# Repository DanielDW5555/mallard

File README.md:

# mallard
Ecological monitoring capstone for ECE 7000. The design will be a continuous redox measurement tool for peatlands.

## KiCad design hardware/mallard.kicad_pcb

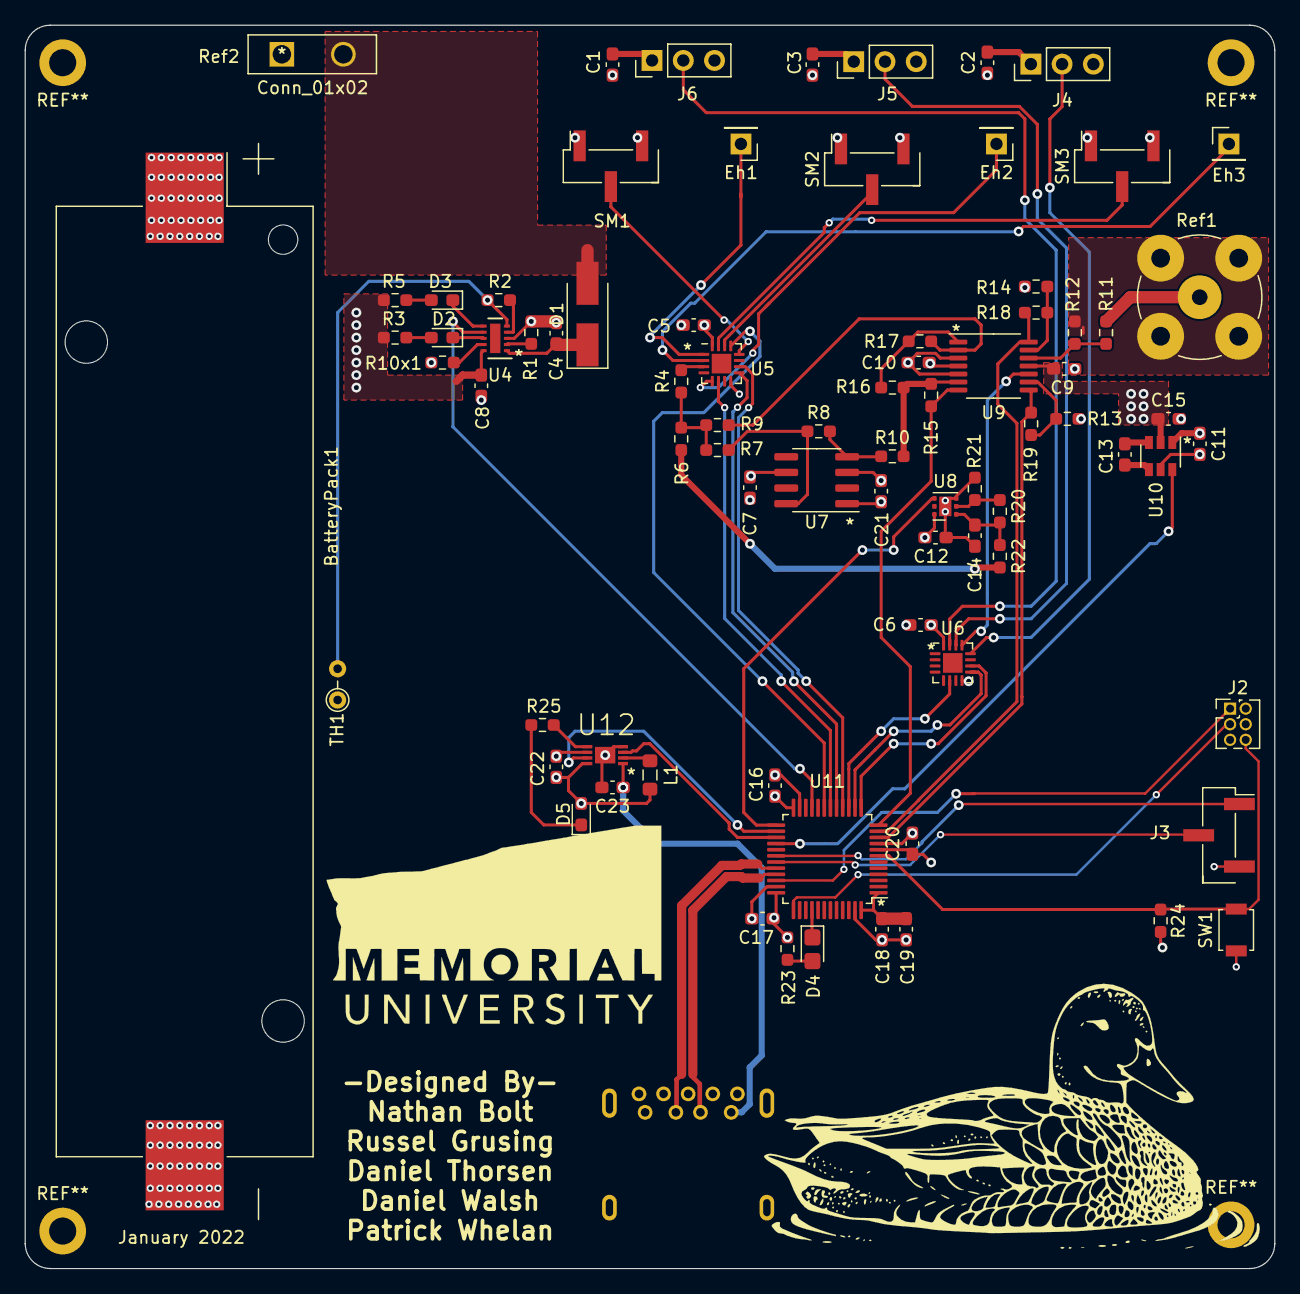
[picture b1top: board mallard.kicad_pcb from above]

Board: 4 copper layers, 101.6 x 101.1 mm, 81 parts (1 on the bottom side), 68 nets.

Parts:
BatteryPack1: 3.7V; BatteryHolder_Keystone_1042_1x18650
C1, C2, C3, C4, C5, C6, C7, C8, C9, C10, C12, C13, C14, C21: 1uF; C_0603_1608Metric_Pad1.08x0.95mm_HandSolder
C11, C15, C23: 10uF; C_0603_1608Metric_Pad1.08x0.95mm_HandSolder
C16, C17, C18, C19, C20: 0.1uF; C_0603_1608Metric_Pad1.08x0.95mm_HandSolder
C22: 3.3uF; C_0603_1608Metric_Pad1.08x0.95mm_HandSolder
D1: D; D_SMA_Handsoldering
D2, D3: LED; LED_0603_1608Metric_Pad1.05x0.95mm_HandSolder
D4: Orange; D_0805_2012Metric_Castellated
D5: RED; LED_0603_1608Metric_Pad1.05x0.95mm_HandSolder
Eh1, Eh2, Eh3: Eh Electrode; PinHeader_1x01_P2.54mm_Vertical
J1: USB_A; USB3_A_Molex_48393-001
J2: Conn_02x03_Odd_Even; PinHeader_2x03_P1.27mm_Vertical
J3: Conn_01x03; PinHeader_1x03_P2.54mm_Vertical_SMD_Pin1Right
J4, J5, J6: Conn_01x03; PinHeader_1x03_P2.54mm_Vertical
L1: 4.7uH; L_0805_2012Metric_Pad1.05x1.20mm_HandSolder
R1, R10x1: 5.1k; R_0603_1608Metric_Pad0.98x0.95mm_HandSolder
R2: 21.5k; R_0603_1608Metric_Pad0.98x0.95mm_HandSolder
R3, R5: 3.6k; R_0603_1608Metric_Pad0.98x0.95mm_HandSolder
R4, R6, R8, R13, R17, R24: 10k; R_0603_1608Metric_Pad0.98x0.95mm_HandSolder
R7, R11, R12, R22: Jumper; R_0603_1608Metric_Pad0.98x0.95mm_HandSolder
R9: Jumper DNI; R_0603_1608Metric_Pad0.98x0.95mm_HandSolder
R10, R19: 20k; R_0603_1608Metric_Pad0.98x0.95mm_HandSolder
R14: 1k; R_0603_1608Metric_Pad0.98x0.95mm_HandSolder
R15: 30k; R_0603_1608Metric_Pad0.98x0.95mm_HandSolder
R16: 20k DNI; R_0603_1608Metric_Pad0.98x0.95mm_HandSolder
R18: 9.1k; R_0603_1608Metric_Pad0.98x0.95mm_HandSolder
R20: 80.6k; R_0603_1608Metric_Pad0.98x0.95mm_HandSolder
R21: 324k; R_0603_1608Metric_Pad0.98x0.95mm_HandSolder
R23: 680; R_0603_1608Metric_Pad0.98x0.95mm_HandSolder
R25: 370; R_0603_1608Metric_Pad0.98x0.95mm_HandSolder
Ref1: Conn_01x02; BNC_TEConnectivity_1478204_Vertical
Ref2: Conn_01x02; mallardScrewTerm.
SM1, SM2, SM3: Conn_01x03; PinHeader_1x03_P2.54mm_Vertical_SMD_Pin1Right
SW1: RESET Switch; SW_SPST_B3U-1000P
TH1: 103AT; R_Axial_DIN0204_L3.6mm_D1.6mm_P2.54mm_Vertical
U4: BQ24210DQCT; WSON-10-1EP_2x3mm_P0.5mm_EP0.84x2.4mm
U5, U6: TMUX1309; WQFN-16-1EP_3x3mm_P0.5mm_EP1.6x1.6mm
U7: LMP7721; SOIC-8_3.9x4.9mm_P1.27mm
U8: TPS71710DRVR; WSON-6-1EP_2x2mm_P0.65mm_EP1x1.6mm
U9: LMV554; TSSOP-14_4.4x5mm_P0.65mm
U10: LTC1983ES6-3; SOT-23-6
U11: STM32L4Q5xx; LQFP-48_7x7mm_P0.5mm
U12: LTC3529EDCB; DFN200X300X80-9N

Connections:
5V_RST: U11.26, U12.7
5V_SHDN_L: U11.27, U12.3
+1V0: R6.2, R22.1
+1V0_EN: U8.4, U11.25
+3V3: BatteryPack1.1, C1.1, C2.1, C3.1, C5.1, C6.1, C7.1, C8.1, C10.1, C11.1, C12.1, C16.1, C17.1, C18.1, C19.1, C20.1, C22.1, D5.2, J2.5, J4.1, J5.1, J6.1, L1.1, R3.1, R5.1, R23.1, R24.2, SM1.1, SM2.1, SM3.1, U4.10, U5.16, U6.16, U7.6, U8.6, U9.4, U10.1, U11.1, U11.9, U11.24, U11.36, U11.48, U12.8
+5V: C23.1, J1.1, U12.1
-3V3: C9.1, C15.1, C21.1, U7.3, U9.11, U10.2
-3V3_SHDN_L: U10.6, U11.28
/RESET_L: J2.6, R24.1, SW1.2, U11.7
/SWCLK: J2.3, U11.37
/SWDIO: J2.1, U11.34
/USB+: J1.3, U11.32
/USB-: J1.2, U11.33
Charge_EN: U4.7, U11.21
Eh_Sense: R15.1, U9.7, U11.12
GND: BatteryPack1.2, C1.2, C2.2, C3.2, C4.2, C5.2, C6.2, C7.2, C8.2, C9.2, C10.2, C11.2, C12.2, C14.2, C15.2, C16.2, C17.2, C18.2, C19.2, C20.2, C21.2, C22.2, C23.2, J1.4, J1.5, J2.2, J3.3, J4.3, J5.3, J6.3, R1.2, R10x1.2, R13.1, R14.2, R21.2, Ref2.1, SM1.3, SM2.3, SM3.3, SW1.1, TH1.1, U4.3, U5.8, U6.8, U7.1, U8.3, U8.7, U9.3, U9.5, U10.5, U11.8, U11.23, U11.35, U11.47, U12.4, U12.6, U12.9
MUX1_A0: U5.9, U11.17
MUX1_A1: U5.10, U11.16
MUX1_EN: U5.6, U11.18
MUX2_A0: U6.9, U11.14
MUX2_A1: U6.10, U11.13
MUX2_EN: U6.6, U11.15
Moisture_Sense: U5.13, U11.19
unnamed: C4.1, D1.1, U4.1
unnamed: C13.1, U10.3
unnamed: C13.2, U10.4
unnamed: C14.1, R20.1, R22.2, U8.1
unnamed: D1.2, Ref2.2
unnamed: D2.1, U4.8
unnamed: D2.2, R3.2
unnamed: D3.1, U4.6
unnamed: D3.2, R5.2
unnamed: D4.1, U11.40
unnamed: D4.2, R23.2
unnamed: D5.1, R25.2
unnamed: Eh1.1, U5.1
unnamed: Eh2.1, U5.5
unnamed: Eh3.1, U5.2
unnamed: J4.2, U6.12
unnamed: J5.2, U6.14
unnamed: J6.2, U6.15
unnamed: L1.2, U12.2
unnamed: R1.1, U4.2
unnamed: R2.1, U4.4
unnamed: R2.2, TH1.2, U4.5
unnamed: R4.1, R6.1, R7.2, R9.2
unnamed: R4.2, U5.3
unnamed: R7.1, R8.2, U7.8
unnamed: R10.1, R15.2, R16.2, U9.6
unnamed: R8.1, R10.2, U7.4
unnamed: R10x1.1, U4.9
unnamed: R11.1, R12.1, U9.12
unnamed: R11.2, Ref1.1
unnamed: R12.2, Ref1.2
unnamed: R13.2, R19.2, U9.9
unnamed: R14.1, R18.2, U9.13
unnamed: R16.1, R17.1, U9.1
unnamed: R9.1, R17.2, U9.2
unnamed: R20.2, R21.1, U8.2
unnamed: R25.1, U12.5
unnamed: SM1.2, U5.12
unnamed: SM2.2, U5.14
unnamed: SM3.2, U5.15
unnamed: U6.13, U9.10
Ref_Out: R18.1, U9.14, U11.11
Temp_Sense: R19.1, U9.8, U11.10
USART1_RX: J3.2, U11.31
USART1_TX: J3.1, U11.30

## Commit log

2021-05-30 Created kicad project
2021-06-11 Created blinky on nucleo devboard
2021-07-02 Added resistors
    Added resistors to top level elements
2021-07-03 Removed Resistors
2021-07-16 Started Creating RTC Functions
2021-07-16 Added Internal Wakeup RTC Functions
    Currently commented out because it makes programming the STM much more difficult.
2021-07-16 Added Instrumentation Components To Kicad
    Added SN74HCS153, LMV554, and TMP235.
2021-07-17 Assigned PC0 As ADC1
2021-07-17 Added code in main to read and store from ADC1
2021-07-17 Changed RTC Prescaler To Be Much Larger
2021-07-22 Changed sleep time of RTC to be more reasonable for development
2021-07-27 Started working on demo firmware
2021-07-27 Added symbols for BQ24210DQCT and LTC1983ES6-3
2021-07-28 Create power.pro
    created a schematic for the power system
2021-08-03 Added TMUX1309 symbol
2021-08-04 Added LM554 to instrumentation sch
2021-08-05 Added Instrumentation Circuits
2021-08-05 added blocking diode
2021-10-01 Added all Digikey part numbers. Started MC schematic. Fixed the reference number on some symbols.
2021-10-04 Finished MC design
2021-10-04 Added 1V LDO. Added LDO symbol
2021-11-08 Not sure what changes I made sry
2021-11-10 House Keeping Tasks
    - Modified parts list parameters for various parts
    - Assigned Ref Des to components
    - Changed TPS717 symbol and feedback resistors
2021-11-11 Added more ref des
2022-01-18 Finished adding TMP sensors and footprints
2022-01-19 Added UART connector on STM32
2022-01-20 Added LMP7721
    Added LMP7721 in parallel to op amp A channel circuit. Added jumpers to be able to select path. Added R11 and R12, R8 changed to DNI
2022-01-23 Updated footprint and added decoupling caps
2022-01-23 Schematic prepared for Layout
2022-01-23 Added screw terminals for solar panel, and added a cap
2022-01-24 Schematic finished, layout stared
2022-01-24 Modified footprints and added items to BOM
2022-01-25 Schematic and Layout Finished
    Needs review
2022-01-25 Updated footprints
2022-01-25 Misc kicad meta data
2022-01-25 Finished schematic and layout
    Needs review
2022-01-26 Small layout changes
2022-01-26 Revised layout, fixed schematic errors
2022-01-26 Created new STM32 firmware project with alt. MC
2022-01-26 Changes some components on BOM
2022-01-26 Replaced -3V charge pump with LM828
2022-01-26 Updated temperature sensor PN
2022-01-27 Found alts for passives
2022-01-27 Updated digikey part #
2022-01-31 Tidied up schematic
2022-02-09 Copy Update 1
2022-02-10 Copy Update 2
2022-03-07 STM32_USB_OTG_UPDATE_1
2022-03-11 Labelling & Reassignment
2022-03-19 Expanded firmware to activate regulators and output UART

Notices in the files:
parts and their libraries:
Copyright 2021 Accelerated Designs. All rights reserved.
